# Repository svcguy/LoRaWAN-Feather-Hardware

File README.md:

# LoRaWAN Feather
## Overview
An Adafruit Feather compatiable board that is LoRaWAN compatible.  Designed to work with the Semtech LoRaWAN reference implementation.  Based on the STM32L073 micro and the Dorji DRF1262T radio module (which is based on the SX1262).  The board has the following hardware features:
* LiPo battery connector and charging as warranted by the Feather spec  
* LiPo fuel gauging as expected by the LoRaWAN reference implementation  
* Implements native USB  
* Connections for I2C, SPI, UART, GPIO, Analog and DAC.  
* An efficent DC-DC buck/boost switch mode converter.  
* Includes an ARM Cortex 10pin SWD debug connector  
* Antenna footprint supports edge mount SMA, u.FL and pigtail connections
* Footprint for U8 can support a hard secure element (ATECC608 or compatible) or an I2C FRAM allowing the user to experiment with hardware encryption or be LoRaWAN 1.1 compliant
* Includes one USER button as well as RESET and BOOT buttons  
* Includes one USER LED and a CHARGE LED.

## Changelog
### REV A0
Inital release
### REV B0
* Fix STC3100 grounding
* Make R16,R17 DNP by default
* Bump Bot Silk to REVB0
### REV C0
* Make U8 footprint capable of crypto and fram device
* Minor updates to schematic
* Minor updates to doc prints
* Update bot silk to REV C0

## Open Source
All schematics, pcb files, gerbers, BOM, CPL are available in this repo.  Part numbers for LCSC and Digikey are included

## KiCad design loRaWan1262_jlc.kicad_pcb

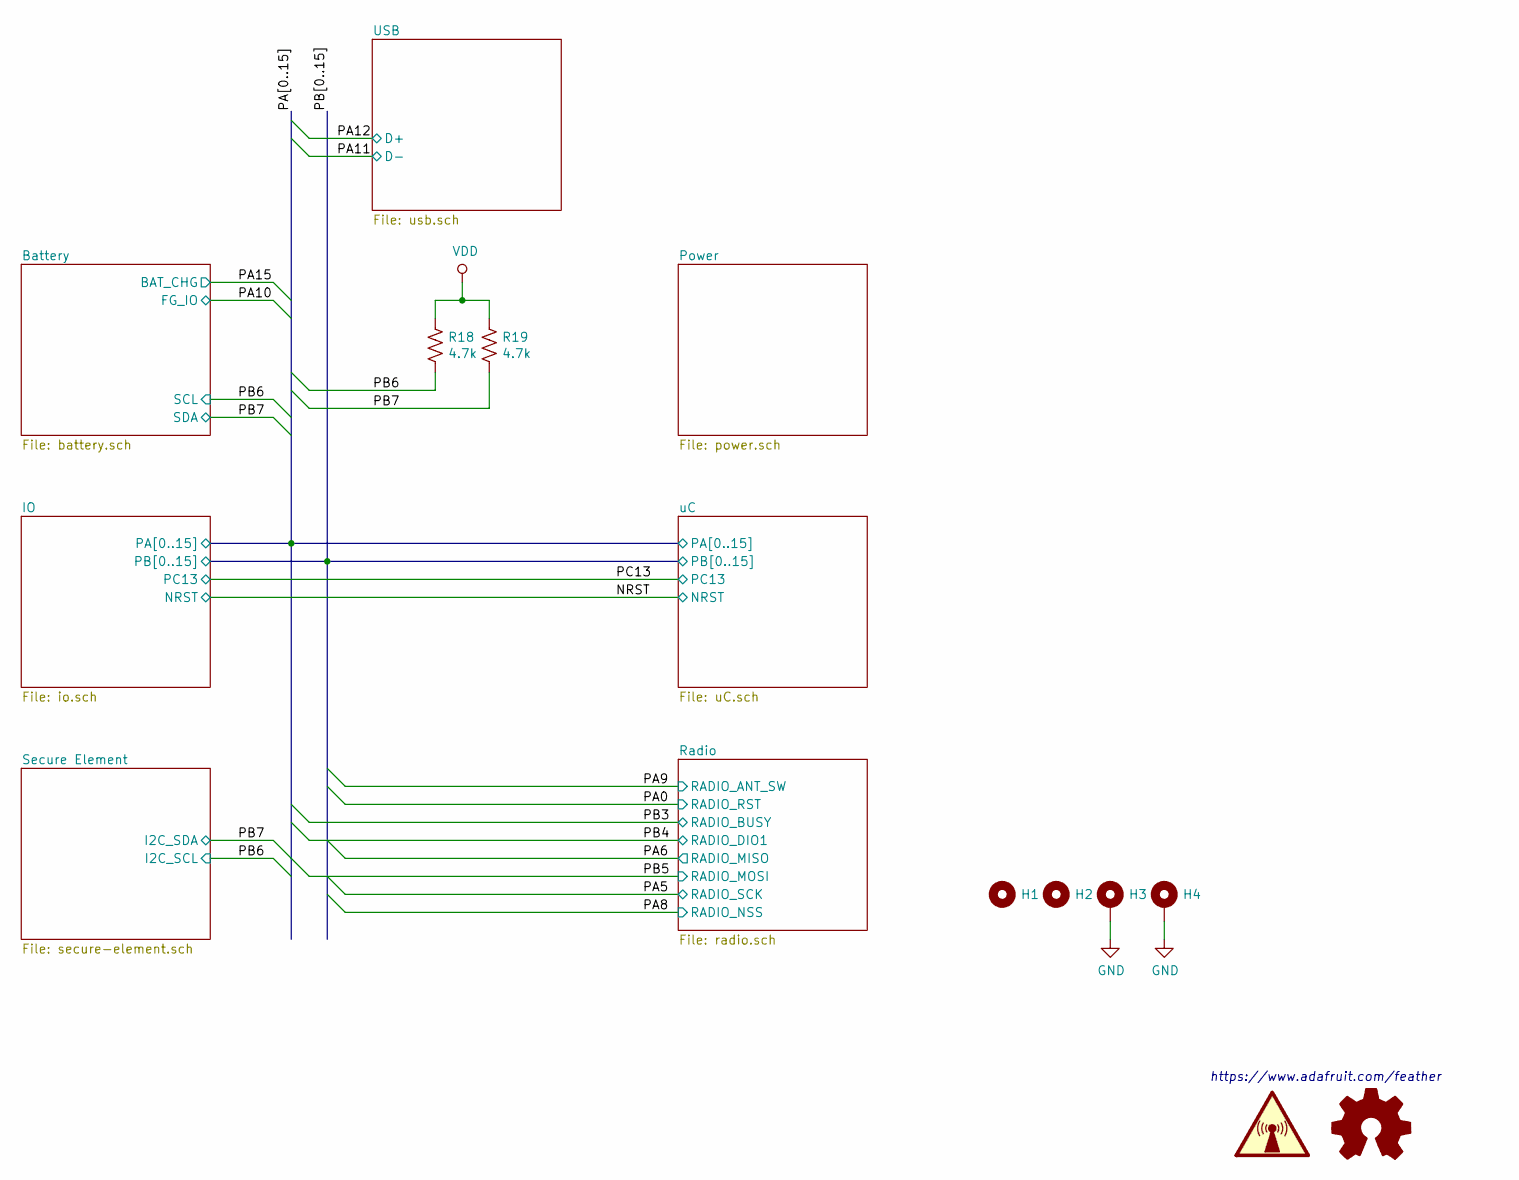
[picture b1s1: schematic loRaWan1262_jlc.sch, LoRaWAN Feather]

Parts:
H1, H2: MountingHole; MountingHole_2.7mm_M2.5; LCSC DNP
H3, H4: MountingHole_Pad; MountingHole_2.7mm_M2.5_Pad; LCSC DNP
R18, R19: 4.7k; R_0402_1005Metric; LCSC C25900

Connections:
/PB6: R18.2; also elsewhere on the board
/PB7: R19.2; also elsewhere on the board
GND: H3.1, H4.1; also elsewhere on the board
VDD: R18.1, R19.1; also elsewhere on the board

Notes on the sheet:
https://www.adafruit.com/feather

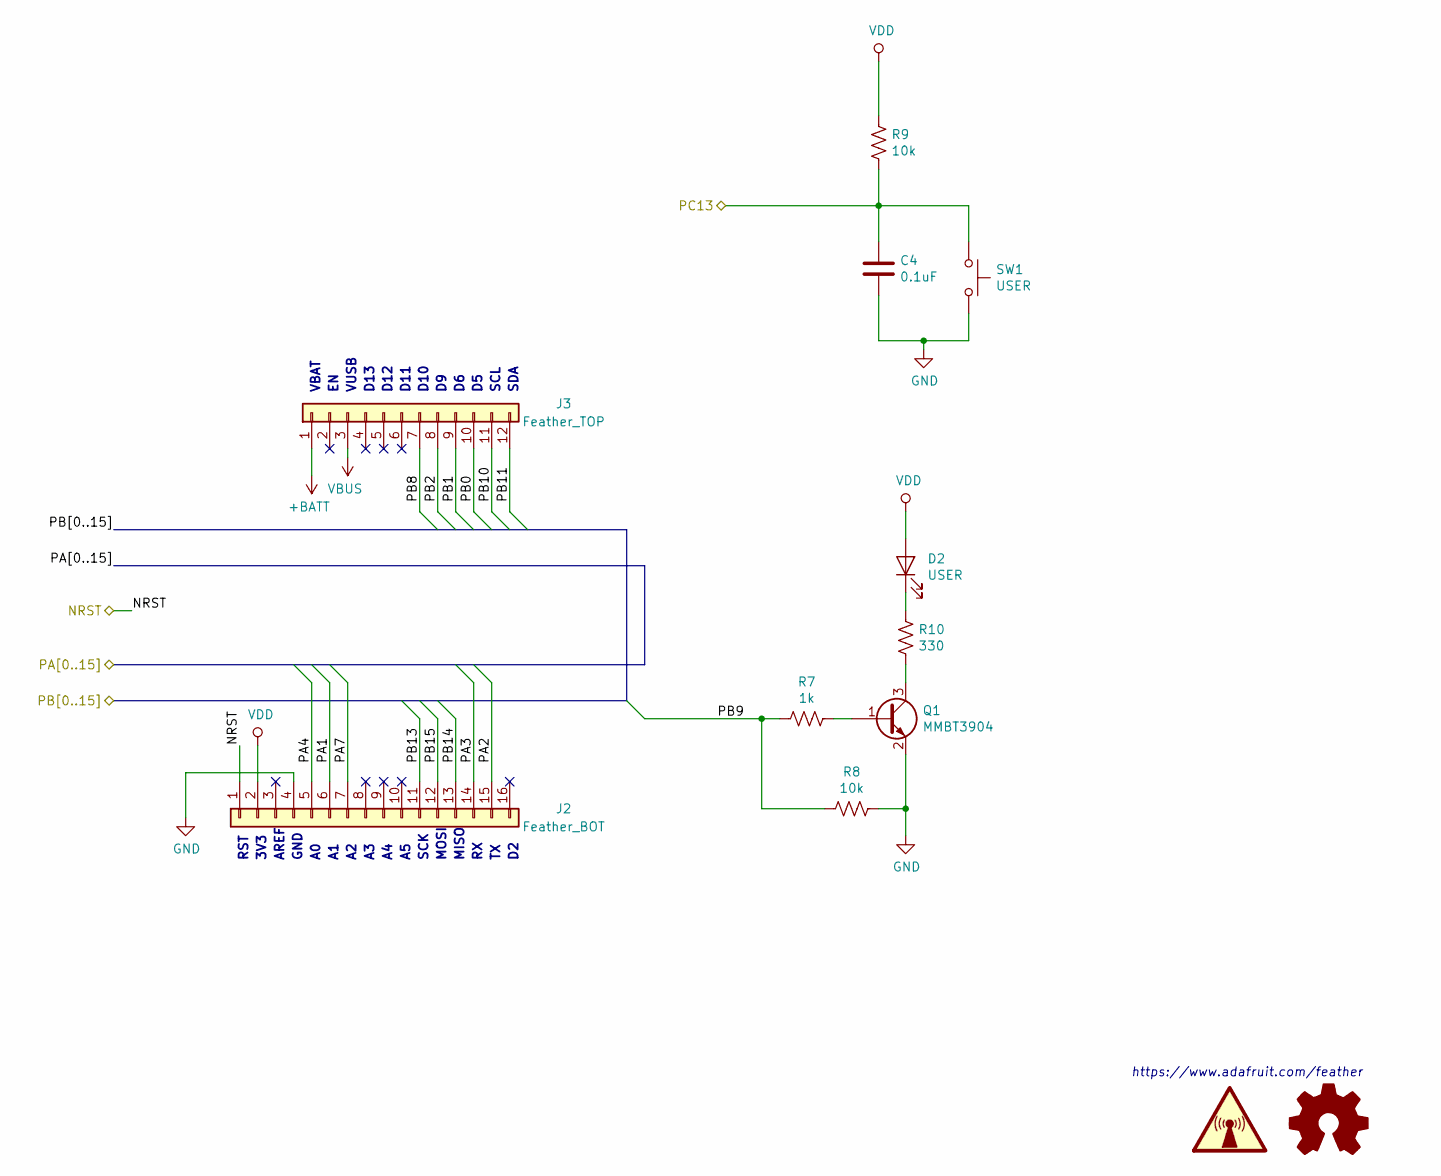
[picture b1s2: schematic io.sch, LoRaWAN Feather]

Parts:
C4: 0.1uF; C_0402_1005Metric; LCSC C1525
D2: USER; LED_0603_1608Metric; LCSC C72043
J2: Feather_BOT; PinHeader_1x16_P2.54mm_Vertical; LCSC DNP
J3: Feather_TOP; PinHeader_1x12_P2.54mm_Vertical; LCSC DNP
Q1: MMBT3904; TSOT-23; LCSC C20526
R7: 1k; R_0402_1005Metric; LCSC C11702
R8, R9: 10k; R_0402_1005Metric; LCSC C25744
R10: 330; R_0402_1005Metric; LCSC C25104
SW1: USER; TS_1187A; LCSC C318884

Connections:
+BATT: J3.1; also elsewhere on the board
/IO/PA1: J2.6; also elsewhere on the board
/IO/PA2: J2.15; also elsewhere on the board
/IO/PA3: J2.14; also elsewhere on the board
/IO/PA4: J2.5; also elsewhere on the board
/IO/PA7: J2.7; also elsewhere on the board
/IO/PB0: J3.10; also elsewhere on the board
/IO/PB1: J3.9; also elsewhere on the board
/IO/PB2: J3.8; also elsewhere on the board
/IO/PB8: J3.7; also elsewhere on the board
/IO/PB9: R7.2, R8.2; also elsewhere on the board
/IO/PB10: J3.11; also elsewhere on the board
/IO/PB11: J3.12; also elsewhere on the board
/IO/PB13: J2.11; also elsewhere on the board
/IO/PB14: J2.13; also elsewhere on the board
/IO/PB15: J2.12; also elsewhere on the board
/NRST: J2.1; also elsewhere on the board
/PC13: C4.1, R9.2, SW1.1; also elsewhere on the board
GND: C4.2, J2.4, Q1.2 (E), R8.1, SW1.2; also elsewhere on the board
unnamed: D2.1 (K), R10.2
unnamed: Q1.1 (B), R7.1
unnamed: Q1.3 (C), R10.1
VBUS: J3.3; also elsewhere on the board
VDD: D2.2 (A), J2.2, R9.1; also elsewhere on the board

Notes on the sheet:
RST
3V3
AREF
GND
SCK
MOSI
MISO
VBAT
VUSB
D13
D12
D11
D10
SCL
SDA
https://www.adafruit.com/feather

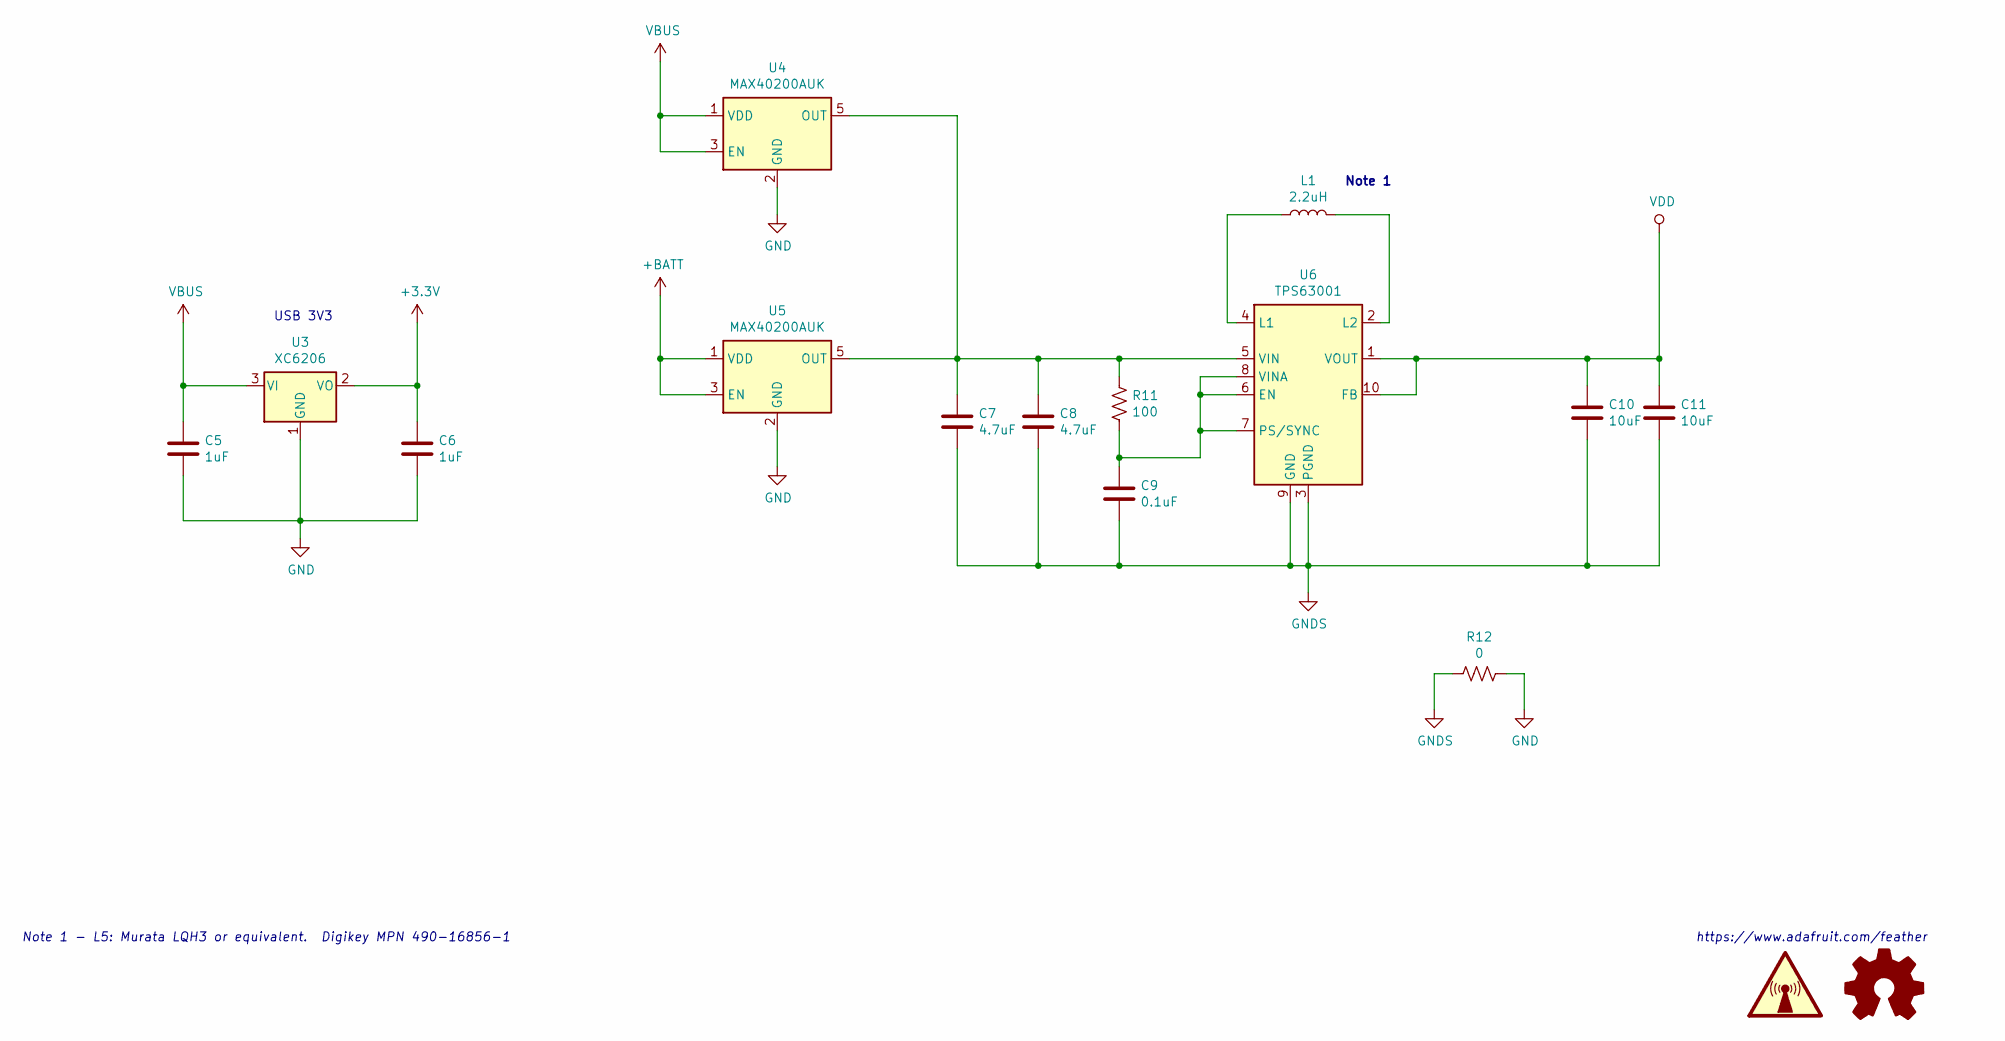
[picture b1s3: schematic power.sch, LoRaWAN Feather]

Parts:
C5, C6: 1uF; C_0402_1005Metric; LCSC C52923
C7, C8: 4.7uF; C_0805_2012Metric; LCSC C1779
C9: 0.1uF; C_0402_1005Metric; LCSC C1525
C10, C11: 10uF; C_0805_2012Metric; LCSC C15850
L1: 2.2uH; L_1210_3225Metric; LCSC C86074
R11: 100; R_0402_1005Metric; LCSC C25076
R12: 0; R_0402_1005Metric; LCSC C17168
U3: XC6206; TSOT-23; LCSC C5446
U4, U5: MAX40200AUK; SOT-23-5; Digikey MAX40200AUK+TCT-ND
U6: TPS63001; Texas_S-PVSON-N10_ThermalVias; LCSC C28060

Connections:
+3V3: C6.1, U3.2 (VO); also elsewhere on the board
+BATT: U5.1 (VDD), U5.3 (EN); also elsewhere on the board
GND: C5.2, C6.2, R12.1, U3.1 (GND), U4.2 (GND), U5.2 (GND); also elsewhere on the board
GNDS: C7.2, C8.2, C9.2, C10.2, C11.2, R12.2, U6.3 (PGND), U6.9 (GND), U6.11 (PGND)
unnamed: C7.1, C8.1, R11.1, U4.5 (OUT), U5.5 (OUT), U6.5 (VIN)
unnamed: C9.1, R11.2, U6.6 (EN), U6.7 (PS/SYNC), U6.8 (VINA)
unnamed: L1.1, U6.4 (L1)
unnamed: L1.2, U6.2 (L2)
VBUS: C5.1, U3.3 (VI), U4.1 (VDD), U4.3 (EN); also elsewhere on the board
VDD: C10.1, C11.1, U6.1 (VOUT), U6.10 (FB); also elsewhere on the board

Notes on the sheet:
Note 1
Note 1 - L5: Murata LQH3 or equivalent. Digikey MPN 490-16856-1
USB 3V3
https://www.adafruit.com/feather

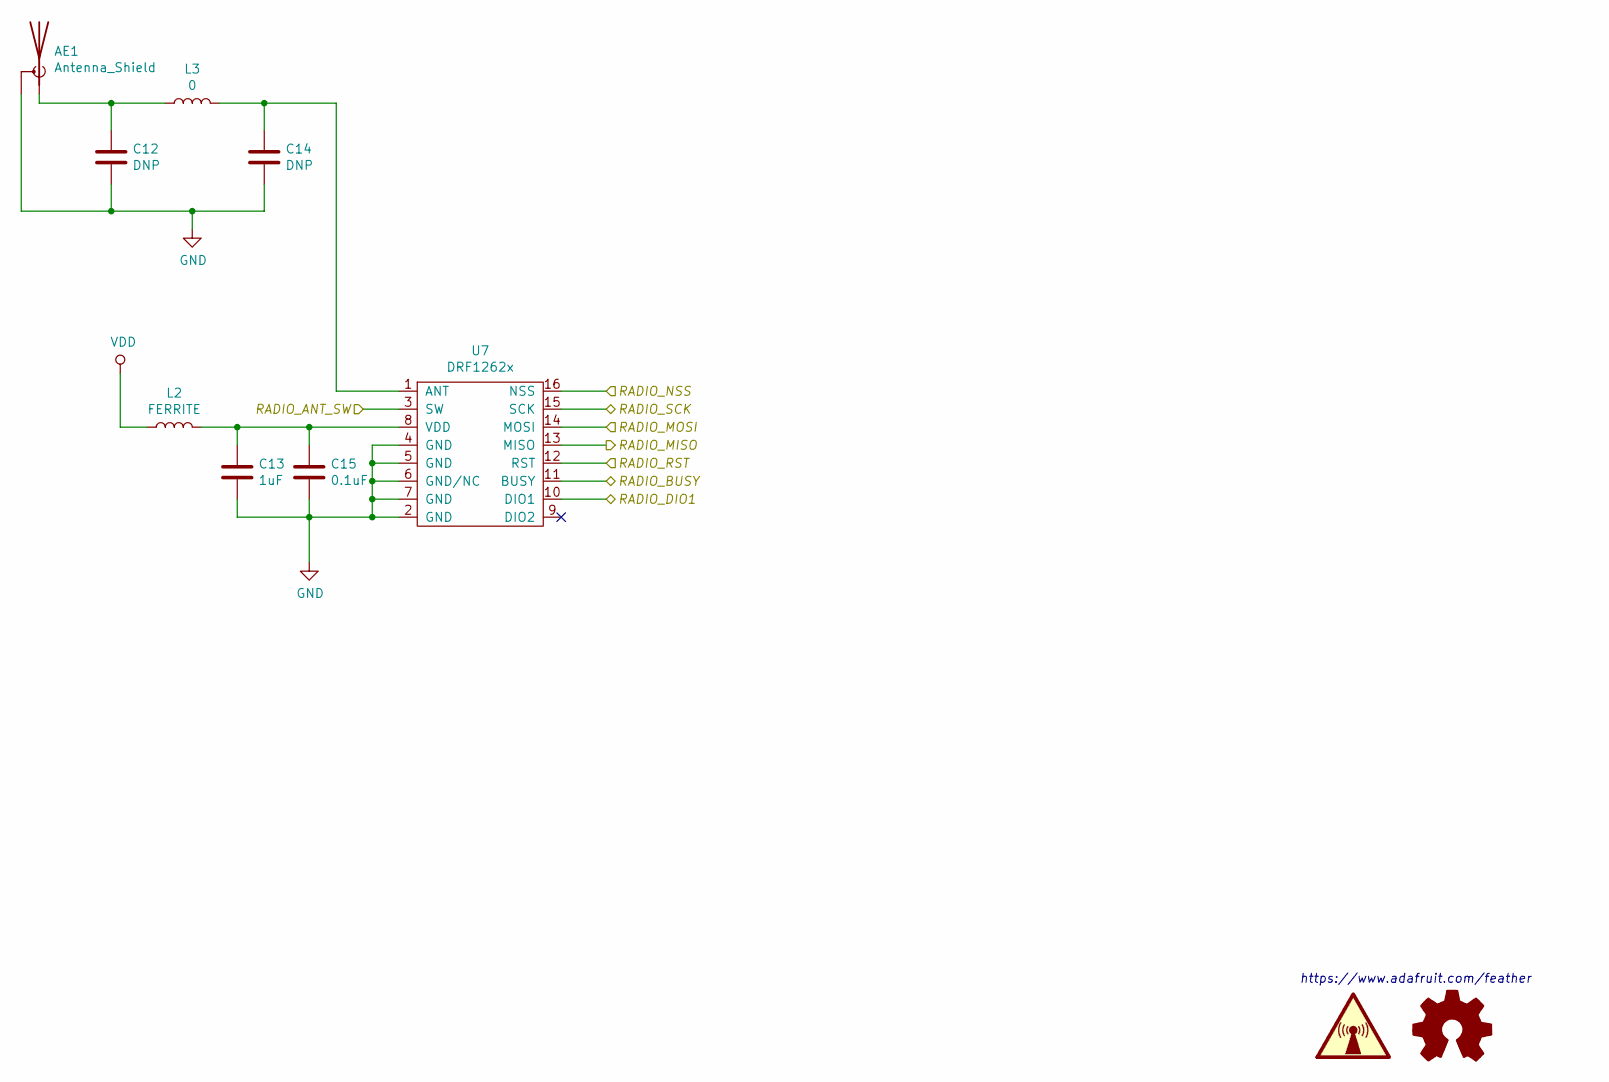
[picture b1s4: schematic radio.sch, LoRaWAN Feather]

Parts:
AE1: Antenna_Shield; RF_ANT; LCSC C129604
C12: DNP; R_0402_1005Metric; LCSC DNP
C13: 1uF; C_0402_1005Metric; LCSC C52923
C14: DNP; C_0402_1005Metric; LCSC DNP
C15: 0.1uF; C_0402_1005Metric; LCSC C1525
L2: FERRITE; R_0805_2012Metric; LCSC C1015
L3: 0; L_0402_1005Metric; LCSC C17168
U7: DRF1262x; LCSC DNP

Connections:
/PA0: U7.12 (RST); also elsewhere on the board
/PA5: U7.15 (SCK); also elsewhere on the board
/PA6: U7.13 (MISO); also elsewhere on the board
/PA8: U7.16 (NSS); also elsewhere on the board
/PA9: U7.3 (SW); also elsewhere on the board
/PB3: U7.11 (BUSY); also elsewhere on the board
/PB4: U7.10 (DIO1); also elsewhere on the board
/PB5: U7.14 (MOSI); also elsewhere on the board
GND: AE1.2 (Shield), C12.2, C13.2, C14.2, C15.2, U7.2 (GND), U7.4 (GND), U7.5 (GND), U7.6 (GND/NC), U7.7 (GND); also elsewhere on the board
unnamed: AE1.1 (A), C12.1, L3.1
unnamed: C13.1, C15.1, L2.2, U7.8 (VDD)
unnamed: C14.1, L3.2, U7.1 (ANT)
VDD: L2.1; also elsewhere on the board

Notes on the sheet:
https://www.adafruit.com/feather

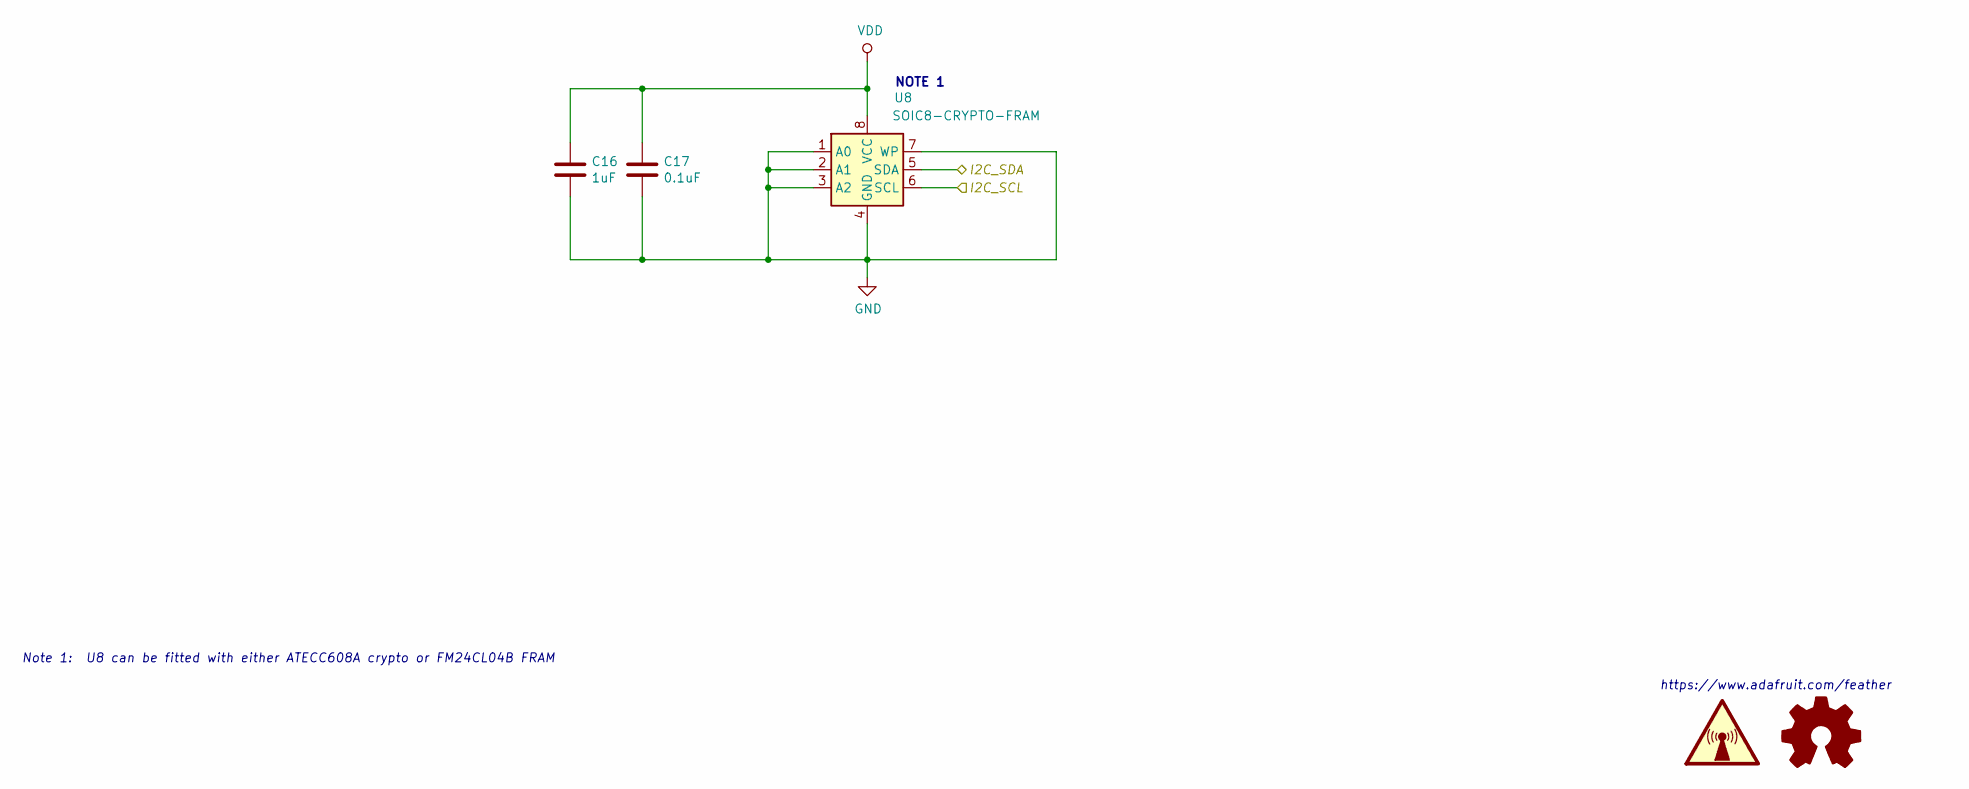
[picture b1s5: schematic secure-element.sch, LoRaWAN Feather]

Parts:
C16: 1uF; C_0402_1005Metric; LCSC C52923
C17: 0.1uF; C_0402_1005Metric; LCSC C1525
U8: SOIC8-CRYPTO-FRAM; SOIC-8_3.9x4.9mm_P1.27mm

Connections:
/PB6: U8.6 (SCL); also elsewhere on the board
/PB7: U8.5 (SDA); also elsewhere on the board
GND: C16.2, C17.2, U8.1 (A0), U8.2 (A1), U8.3 (A2), U8.4 (GND), U8.7 (WP); also elsewhere on the board
VDD: C16.1, C17.1, U8.8 (VCC); also elsewhere on the board

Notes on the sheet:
https://www.adafruit.com/feather
NOTE 1
Note 1: U8 can be fitted with either ATECC608A crypto or FM24CL04B FRAM

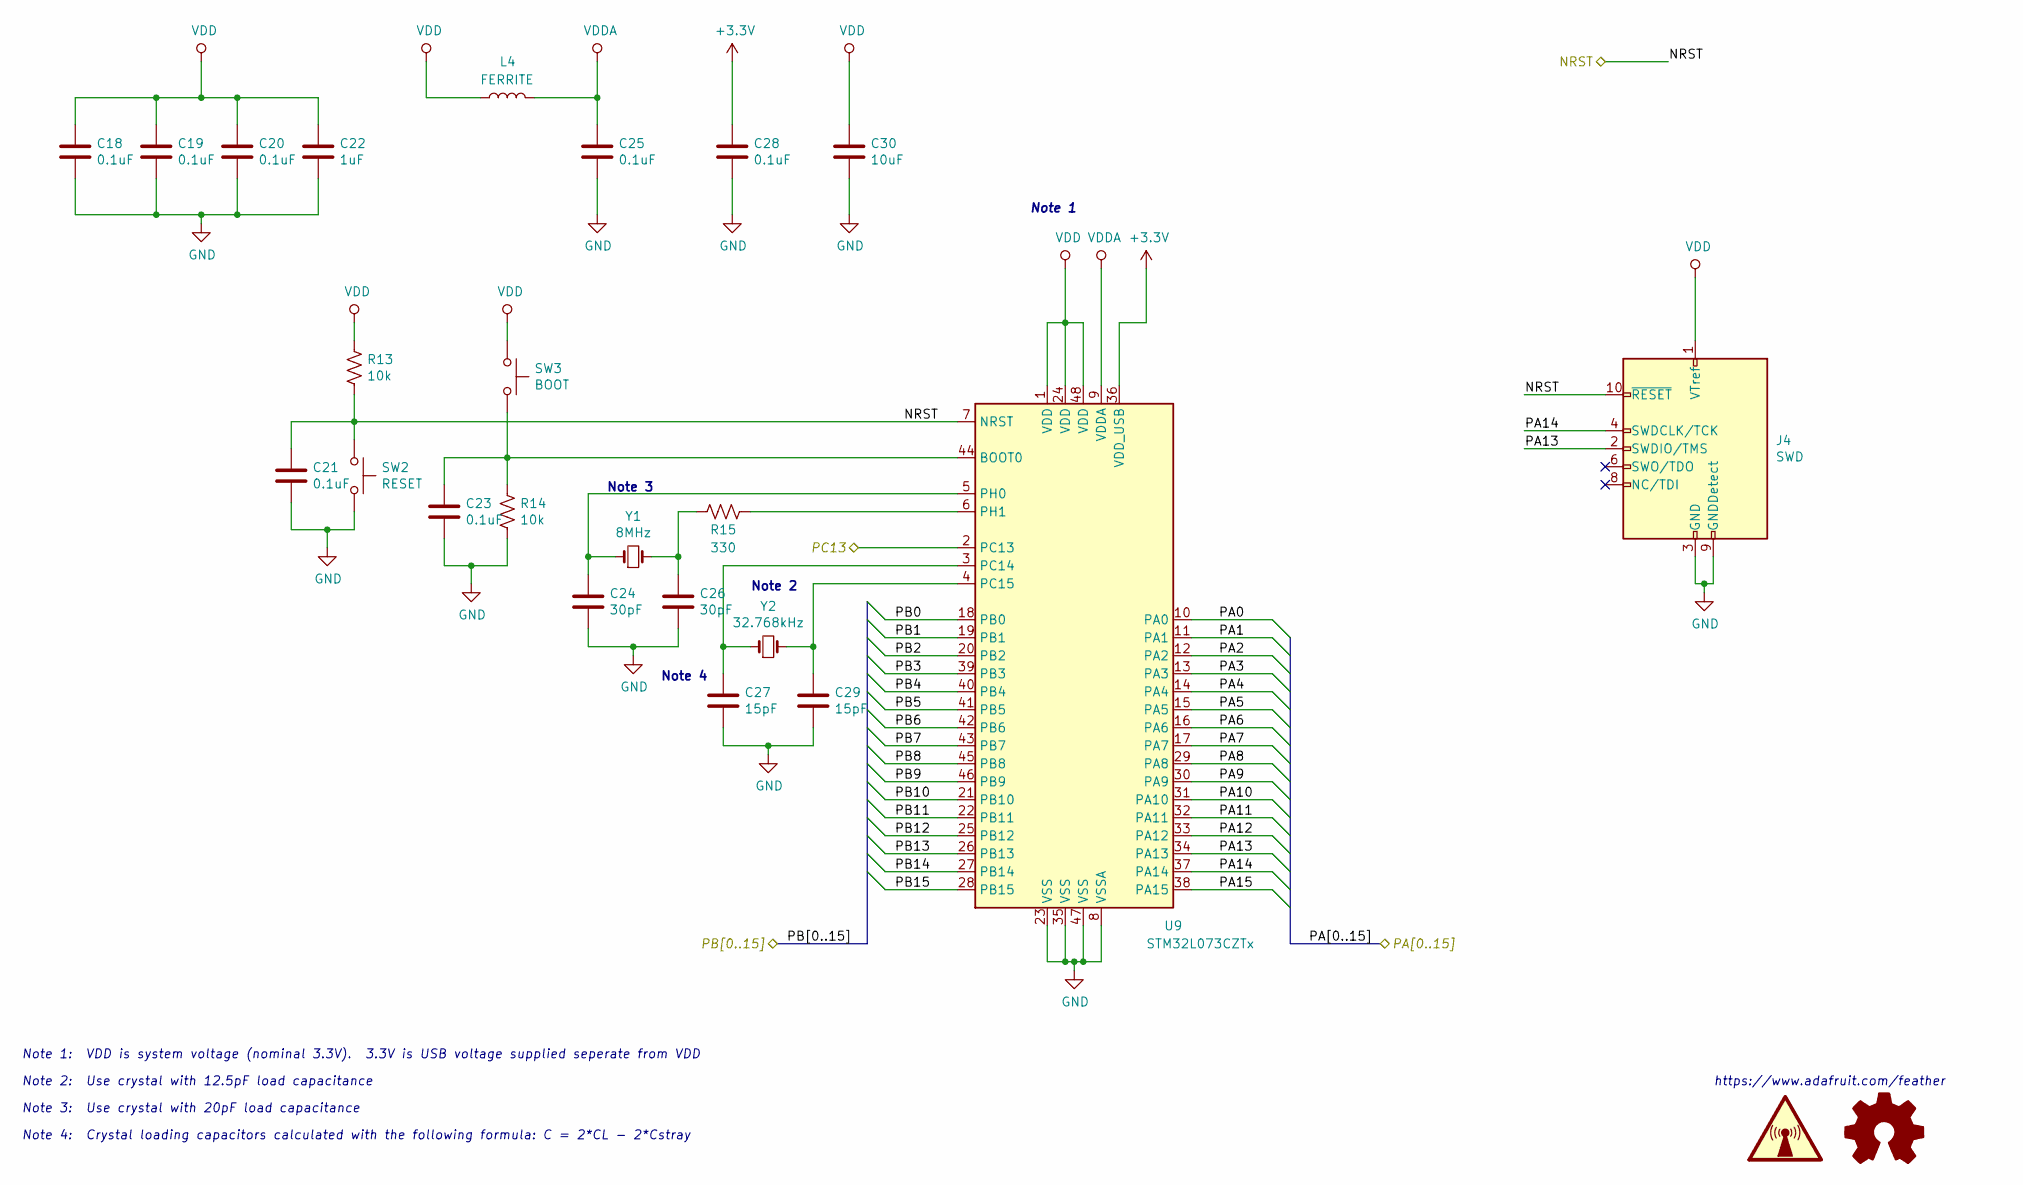
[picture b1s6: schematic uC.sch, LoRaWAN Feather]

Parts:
C18, C19, C20, C21, C23, C25, C28: 0.1uF; C_0402_1005Metric; LCSC C1525
C22: 1uF; C_0402_1005Metric; LCSC C52923
C24, C26: 30pF; C_0402_1005Metric; LCSC C1570
C27, C29: 15pF; C_0402_1005Metric; LCSC C1548
C30: 10uF; C_0805_2012Metric; LCSC C15850
J4: SWD; PinHeader_2x05_P1.27mm_Vertical_SMD; LCSC DNP
L4: FERRITE; L_0805_2012Metric; LCSC C1015
R13, R14: 10k; R_0402_1005Metric; LCSC C25744
R15: 330; R_0402_1005Metric; LCSC C25104
SW2: RESET; TS_1187A; LCSC C318884
SW3: BOOT; TS_1187A; LCSC C318884
U9: STM32L073CZTx; LQFP-48_7x7mm_P0.5mm; LCSC DNP
Y1: 8MHz; Crystal_SMD_Abracon_ABM3-2Pin_5.0x3.2mm; LCSC C115962
Y2: 32.768kHz; Crystal_SMD_3215-2Pin_3.2x1.5mm; LCSC C32346

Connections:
+3V3: C28.1, U9.36 (VDD_USB); also elsewhere on the board
/IO/PA1: U9.11 (PA1); also elsewhere on the board
/IO/PA2: U9.12 (PA2); also elsewhere on the board
/IO/PA3: U9.13 (PA3); also elsewhere on the board
/IO/PA4: U9.14 (PA4); also elsewhere on the board
/IO/PA7: U9.17 (PA7); also elsewhere on the board
/IO/PB0: U9.18 (PB0); also elsewhere on the board
/IO/PB1: U9.19 (PB1); also elsewhere on the board
/IO/PB2: U9.20 (PB2); also elsewhere on the board
/IO/PB8: U9.45 (PB8); also elsewhere on the board
/IO/PB9: U9.46 (PB9); also elsewhere on the board
/IO/PB10: U9.21 (PB10); also elsewhere on the board
/IO/PB11: U9.22 (PB11); also elsewhere on the board
/IO/PB13: U9.26 (PB13); also elsewhere on the board
/IO/PB14: U9.27 (PB14); also elsewhere on the board
/IO/PB15: U9.28 (PB15); also elsewhere on the board
/NRST: C21.1, J4.10 (~RESET~), R13.2, SW2.1, U9.7 (NRST); also elsewhere on the board
/PA0: U9.10 (PA0); also elsewhere on the board
/PA5: U9.15 (PA5); also elsewhere on the board
/PA6: U9.16 (PA6); also elsewhere on the board
/PA8: U9.29 (PA8); also elsewhere on the board
/PA9: U9.30 (PA9); also elsewhere on the board
/PA10: U9.31 (PA10); also elsewhere on the board
/PA15: U9.38 (PA15); also elsewhere on the board
/PB3: U9.39 (PB3); also elsewhere on the board
/PB4: U9.40 (PB4); also elsewhere on the board
/PB5: U9.41 (PB5); also elsewhere on the board
/PB6: U9.42 (PB6); also elsewhere on the board
/PB7: U9.43 (PB7); also elsewhere on the board
/PC13: U9.2 (PC13); also elsewhere on the board
/uC/PA13: J4.2 (SWDIO/TMS), U9.34 (PA13)
/uC/PA14: J4.4 (SWDCLK/TCK), U9.37 (PA14)
D+: U9.33 (PA12); also elsewhere on the board
D-: U9.32 (PA11); also elsewhere on the board
GND: C18.2, C19.2, C20.2, C21.2, C22.2, C23.2, C24.2, C25.2, C26.2, C27.2, C28.2, C29.2, C30.2, J4.3 (GND), J4.5 (GND), J4.9 (GNDDetect), R14.2, SW2.2, U9.8 (VSSA), U9.23 (VSS), U9.35 (VSS), U9.47 (VSS); also elsewhere on the board
unnamed: C23.1, R14.1, SW3.2, U9.44 (BOOT0)
unnamed: C24.1, U9.5 (PH0), Y1.1
unnamed: C26.1, R15.2, Y1.2
unnamed: C27.1, U9.3 (PC14), Y2.1
unnamed: C29.1, U9.4 (PC15), Y2.2
unnamed: R15.1, U9.6 (PH1)
VDD: C18.1, C19.1, C20.1, C22.1, C30.1, J4.1 (VTref), L4.2, R13.1, SW3.1, U9.1 (VDD), U9.24 (VDD), U9.48 (VDD); also elsewhere on the board
VDDA: C25.1, L4.1, U9.9 (VDDA)

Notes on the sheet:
Note 1
Note 1: VDD is system voltage (nominal 3.3V). 3.3V is USB voltage supplied seperate from VDD
Note 2
Note 3
Note 2: Use crystal with 12.5pF load capacitance
Note 3: Use crystal with 20pF load capacitance
Note 4: Crystal loading capacitors calculated with the following formula: C = 2*CL - 2*Cstray
Note 4
https://www.adafruit.com/feather

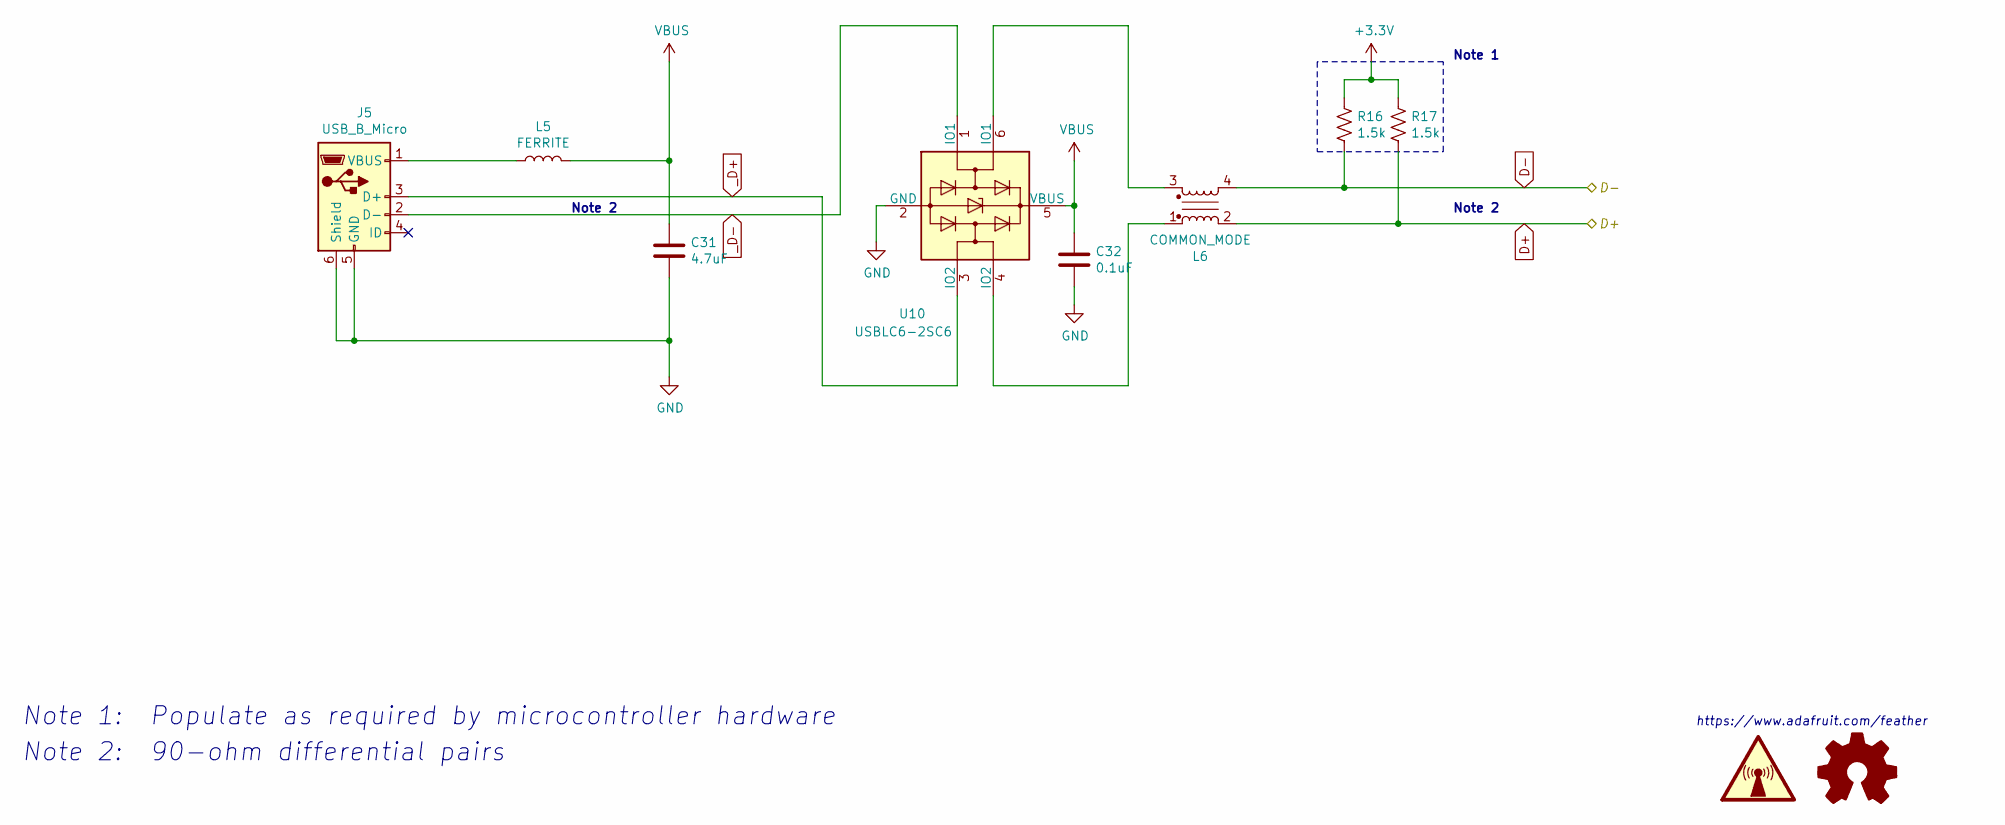
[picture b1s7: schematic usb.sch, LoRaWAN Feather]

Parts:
C31: 4.7uF; C_0805_2012Metric; LCSC C1779
C32: 0.1uF; C_0402_1005Metric; LCSC C1525
J5: USB_B_Micro; USB_Micro-B_Amphenol_10103594-0001LF_Horizontal; LCSC C428495
L5: FERRITE; L_0805_2012Metric; LCSC C1015
L6: COMMON_MODE; COMMON_MODE_FILTER_0805; LCSC C86163
R16, R17: 1.5k; R_0402_1005Metric; LCSC C25867
U10: USBLC6-2SC6; TSOT-23-6; LCSC C7519

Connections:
+3V3: R16.1, R17.1; also elsewhere on the board
D+: L6.2, R17.2; also elsewhere on the board
D-: L6.4, R16.2; also elsewhere on the board
GND: C31.2, C32.2, J5.5 (GND), J5.6 (Shield), U10.2 (GND); also elsewhere on the board
unnamed: J5.1 (VBUS), L5.1
unnamed: L6.1, U10.4 (IO2)
unnamed: L6.3, U10.6 (IO1)
VBUS: C31.1, C32.1, L5.2, U10.5 (VBUS); also elsewhere on the board
_D+: J5.3 (D+), U10.3 (IO2)
_D-: J5.2 (D-), U10.1 (IO1)

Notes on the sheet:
Note 1
Note 1: Populate as required by microcontroller hardware
Note 2
Note 2: 90-ohm differential pairs
https://www.adafruit.com/feather

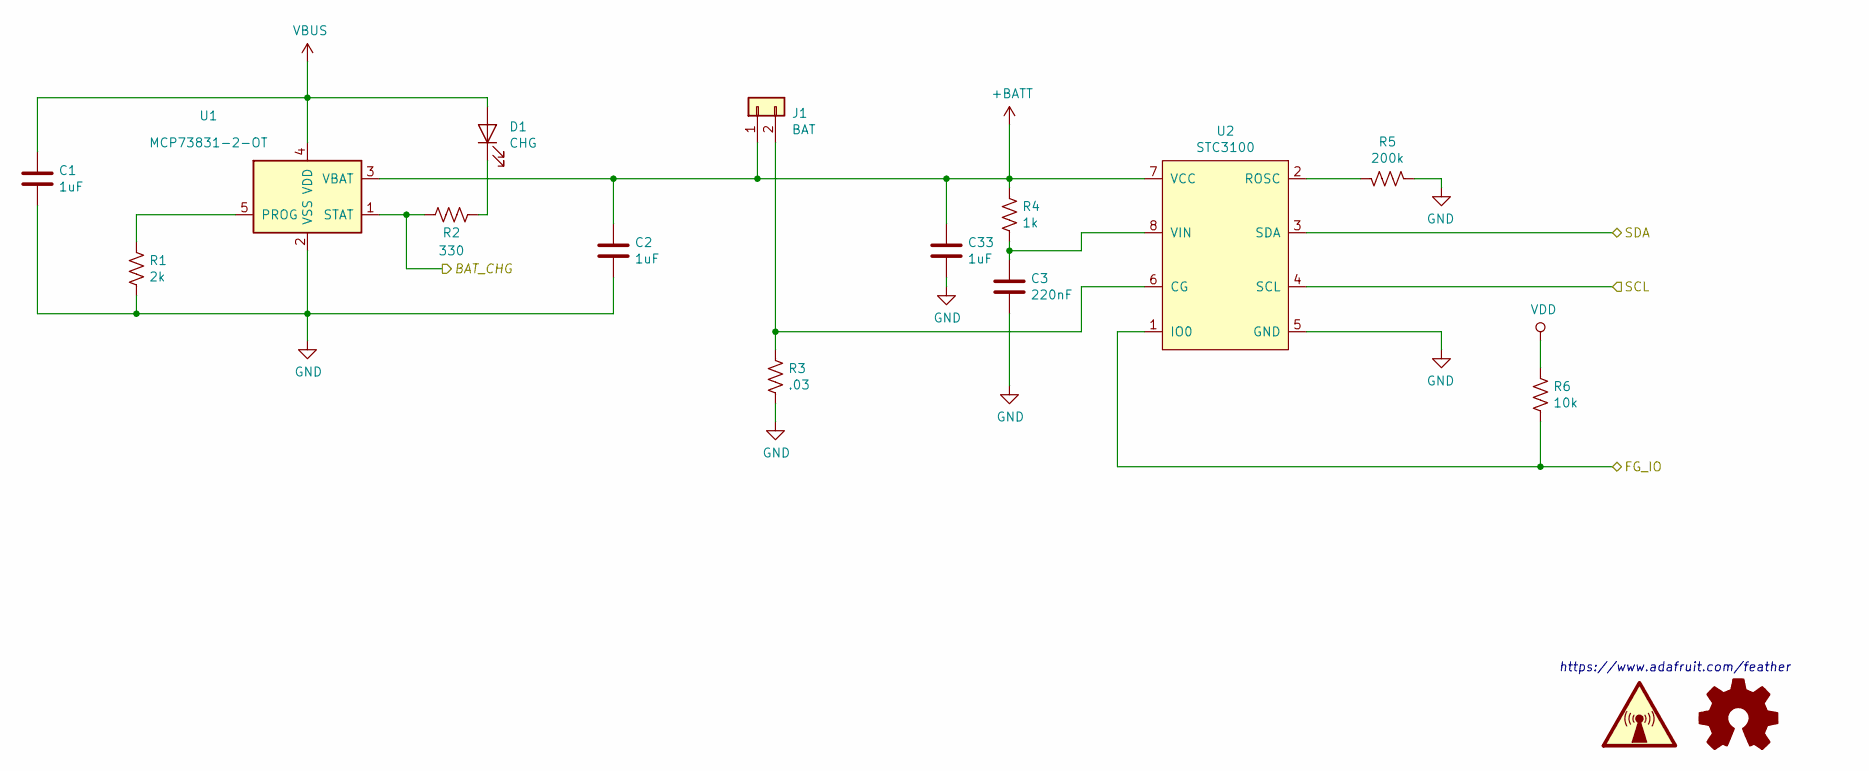
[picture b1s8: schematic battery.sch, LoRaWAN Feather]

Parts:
C1, C2, C33: 1uF; C_0402_1005Metric; LCSC C52923
C3: 220nF; C_0402_1005Metric; LCSC C16772
D1: CHG; LED_0603_1608Metric; LCSC C72038
J1: BAT; JST_PH_S2B-PH-SM4-TB_1x02-1MP_P2.00mm_Horizontal; Digikey 455-1749-1-ND
R1: 2k; R_0402_1005Metric; LCSC C4109
R2: 330; R_0402_1005Metric; LCSC C25104
R3: .03; R_0805_2012Metric; LCSC C247605
R4: 1k; R_0402_1005Metric; LCSC C11702
R5: 200k; R_0603_1608Metric; LCSC C61953
R6: 10k; R_0402_1005Metric; LCSC C25744
U1: MCP73831-2-OT; TSOT-23-5; LCSC C424093
U2: STC3100; MSOP-8_3x3mm_P0.65mm; Digikey 497-10526-1-ND

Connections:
+BATT: C2.1, C33.1, J1.1, R4.1, U1.3 (VBAT), U2.7 (VCC); also elsewhere on the board
/PA10: R6.2, U2.1 (IO0); also elsewhere on the board
/PA15: R2.2, U1.1 (STAT); also elsewhere on the board
/PB6: U2.4 (SCL); also elsewhere on the board
/PB7: U2.3 (SDA); also elsewhere on the board
GND: C1.2, C2.2, C3.2, C33.2, R1.2, R3.2, R5.2, U1.2 (VSS), U2.5 (GND); also elsewhere on the board
unnamed: C3.1, R4.2, U2.8 (VIN)
unnamed: D1.1 (K), R2.1
unnamed: J1.2, R3.1, U2.6 (CG)
unnamed: R1.1, U1.5 (PROG)
unnamed: R5.1, U2.2 (ROSC)
VBUS: C1.1, D1.2 (A), U1.4 (VDD); also elsewhere on the board
VDD: R6.1; also elsewhere on the board

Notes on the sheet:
https://www.adafruit.com/feather

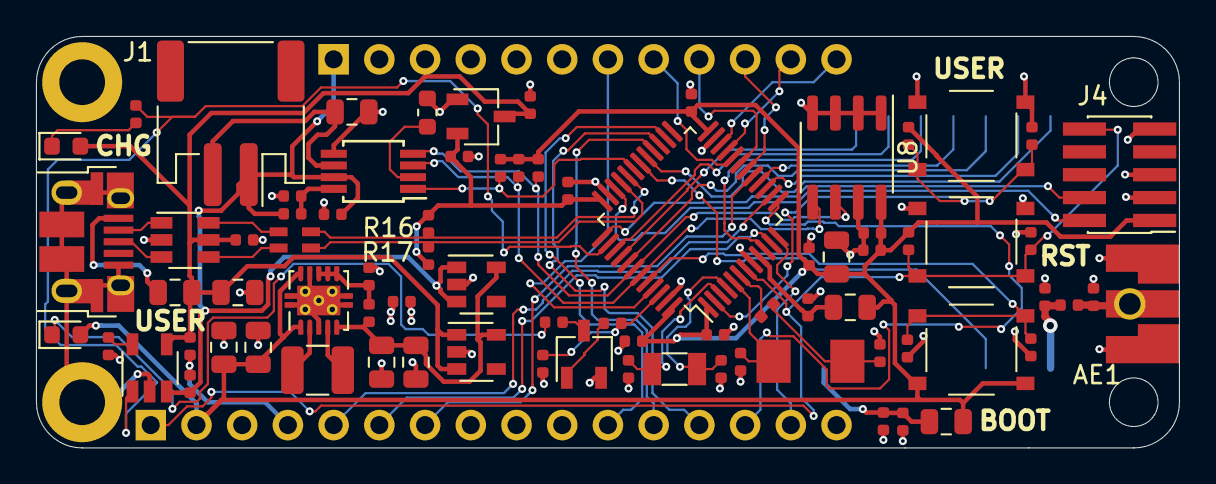
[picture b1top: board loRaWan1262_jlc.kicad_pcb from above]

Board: 2 copper layers, 63.5 x 22.9 mm, 86 parts (1 on the bottom side), 66 nets.

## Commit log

2019-11-18 Inital commit
2019-11-18 Add README draft, add 3d image
2019-11-18 Add .gitignore, cleanup README
2019-11-19 Add digikey pn's to schematic, update BOM
2019-12-21 PCB REV B0 * Fix STC3100 grounding * Make R16,R17 DNP by default * Bump Bot Silk to REVB0
2020-01-02 PCB REV C0 * Make U8 footprint capable of crypto and fram device * Minor updates to schematic * Minor updates to doc prints * Update bot silk to REV C0
2020-01-02 Add datasheets for crypto and fram devices
